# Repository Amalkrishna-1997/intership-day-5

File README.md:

# intership-day-5
internship day 5
PCB layout designing by KICad,

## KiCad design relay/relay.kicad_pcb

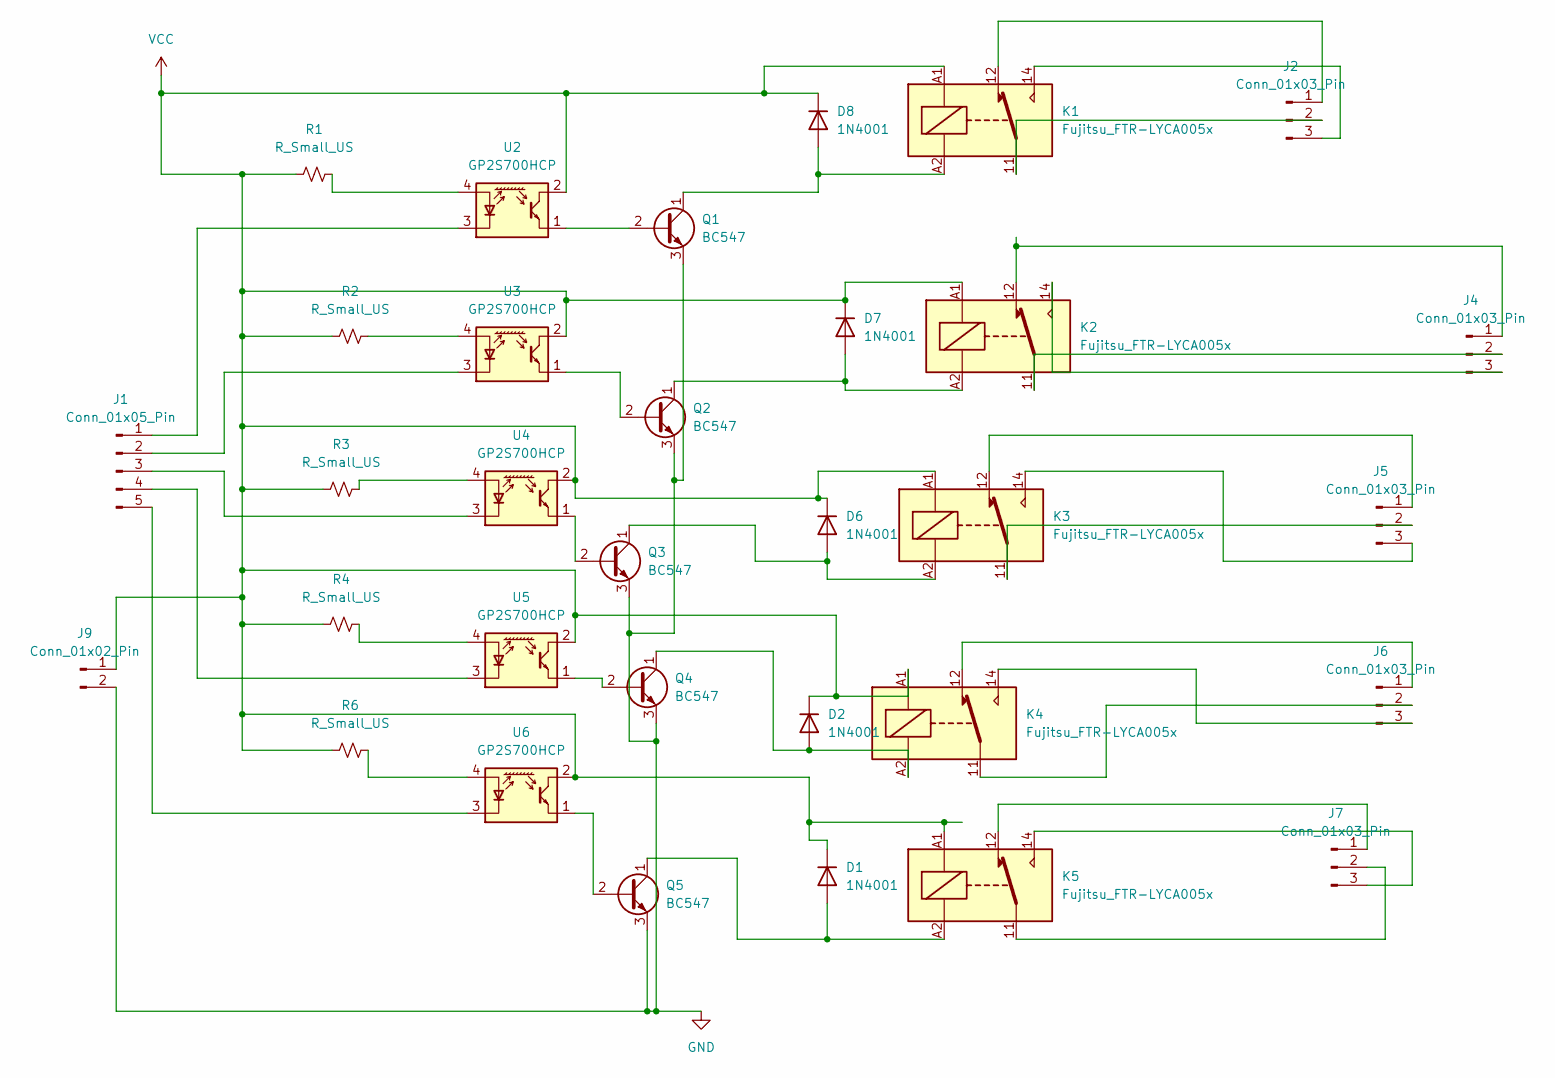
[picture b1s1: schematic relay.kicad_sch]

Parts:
D1, D2, D6, D7, D8: 1N4001; D_DO-41_SOD81_P10.16mm_Horizontal
J1: Conn_01x05_Pin; PinHeader_1x05_P1.00mm_Vertical
J2, J4, J5, J6, J7: Conn_01x03_Pin; PinHeader_1x03_P1.00mm_Vertical
J9: Conn_01x02_Pin; PinHeader_1x02_P1.00mm_Vertical
K1, K2, K3, K4, K5: Fujitsu_FTR-LYCA005x; Relay_SPDT_Schrack-RP-II-1-FormC_RM3.5mm
Q1, Q2, Q3, Q4, Q5: BC547; TO-92_Inline
R1, R2, R3, R4, R6: R_Small_US; R_Axial_DIN0207_L6.3mm_D2.5mm_P10.16mm_Horizontal
U2, U3, U4, U5, U6: GP2S700HCP; Everlight_ITR8307F43

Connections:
GND: J9.2, Q1.3 (E), Q2.3 (E), Q3.3 (E), Q4.3 (E), Q5.3 (E)
unnamed: D1.2 (A), K5.A2, Q5.1 (C)
unnamed: D2.2 (A), K4.A2, Q4.1 (C)
unnamed: D6.2 (A), K3.A2, Q3.1 (C)
unnamed: D7.2 (A), K2.A2, Q2.1 (C)
unnamed: D8.2 (A), K1.A2, Q1.1 (C)
unnamed: J1.1, U2.3 (K)
unnamed: J1.2, U3.3 (K)
unnamed: J1.3, U4.3 (K)
unnamed: J1.4, U5.3 (K)
unnamed: J1.5, U6.3 (K)
unnamed: J2.1, K1.12
unnamed: J2.2, K1.11
unnamed: J2.3, K1.14
unnamed: J4.1, K2.12
unnamed: J4.2, K2.11
unnamed: J4.3, K2.14
unnamed: J5.1, K3.12
unnamed: J5.2, K3.11
unnamed: J5.3, K3.14
unnamed: J6.1, K4.12
unnamed: J6.2, K4.11
unnamed: J6.3, K4.14
unnamed: J7.1, K5.12
unnamed: J7.2, K5.11
unnamed: J7.3, K5.14
unnamed: Q1.2 (B), U2.1
unnamed: Q2.2 (B), U3.1
unnamed: Q3.2 (B), U4.1
unnamed: Q4.2 (B), U5.1
unnamed: Q5.2 (B), U6.1
unnamed: R1.1, U2.4 (A)
unnamed: R2.2, U3.4 (A)
unnamed: R3.2, U4.4 (A)
unnamed: R4.2, U5.4 (A)
unnamed: R6.2, U6.4 (A)
VCC: D1.1 (K), D2.1 (K), D6.1 (K), D7.1 (K), D8.1 (K), J9.1, K1.A1, K2.A1, K3.A1, K4.A1, K5.A1, R1.2, R2.1, R3.1, R4.1, R6.1, U2.2, U3.2, U4.2, U5.2, U6.2

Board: 2 copper layers, 32 parts (0 on the bottom side), 37 nets, no tracks yet.

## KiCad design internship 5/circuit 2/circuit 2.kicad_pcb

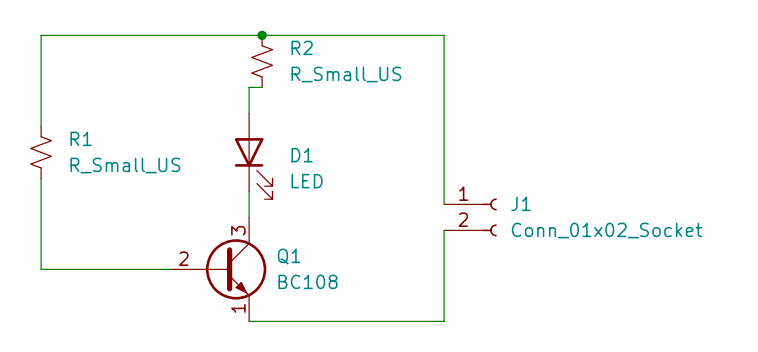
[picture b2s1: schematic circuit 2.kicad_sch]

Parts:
D1: LED; LED_D5.0mm
J1: Conn_01x02_Socket; PinHeader_1x02_P1.00mm_Vertical
Q1: BC108; TO-18-3
R1, R2: R_Small_US; R_Axial_DIN0207_L6.3mm_D2.5mm_P10.16mm_Horizontal

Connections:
unnamed: D1.2 (A), R2.2
unnamed: D1.1 (K), Q1.3 (C)
unnamed: J1.1, R1.1, R2.1
unnamed: J1.2, Q1.1 (E)
unnamed: Q1.2 (B), R1.2

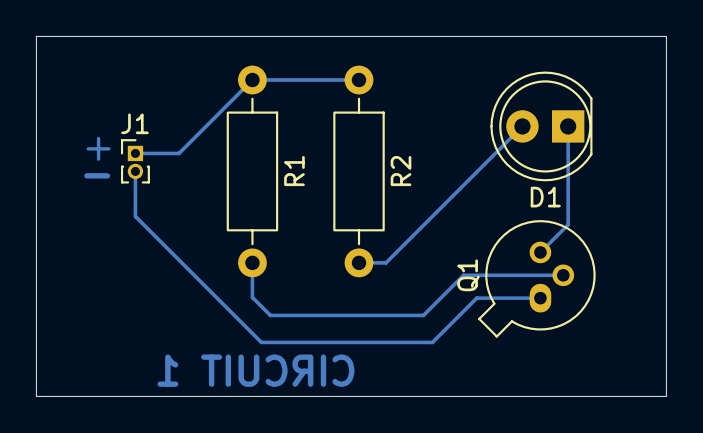
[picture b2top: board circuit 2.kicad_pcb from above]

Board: 2 copper layers, 35.0 x 20.0 mm, 5 parts (0 on the bottom side), 5 nets.

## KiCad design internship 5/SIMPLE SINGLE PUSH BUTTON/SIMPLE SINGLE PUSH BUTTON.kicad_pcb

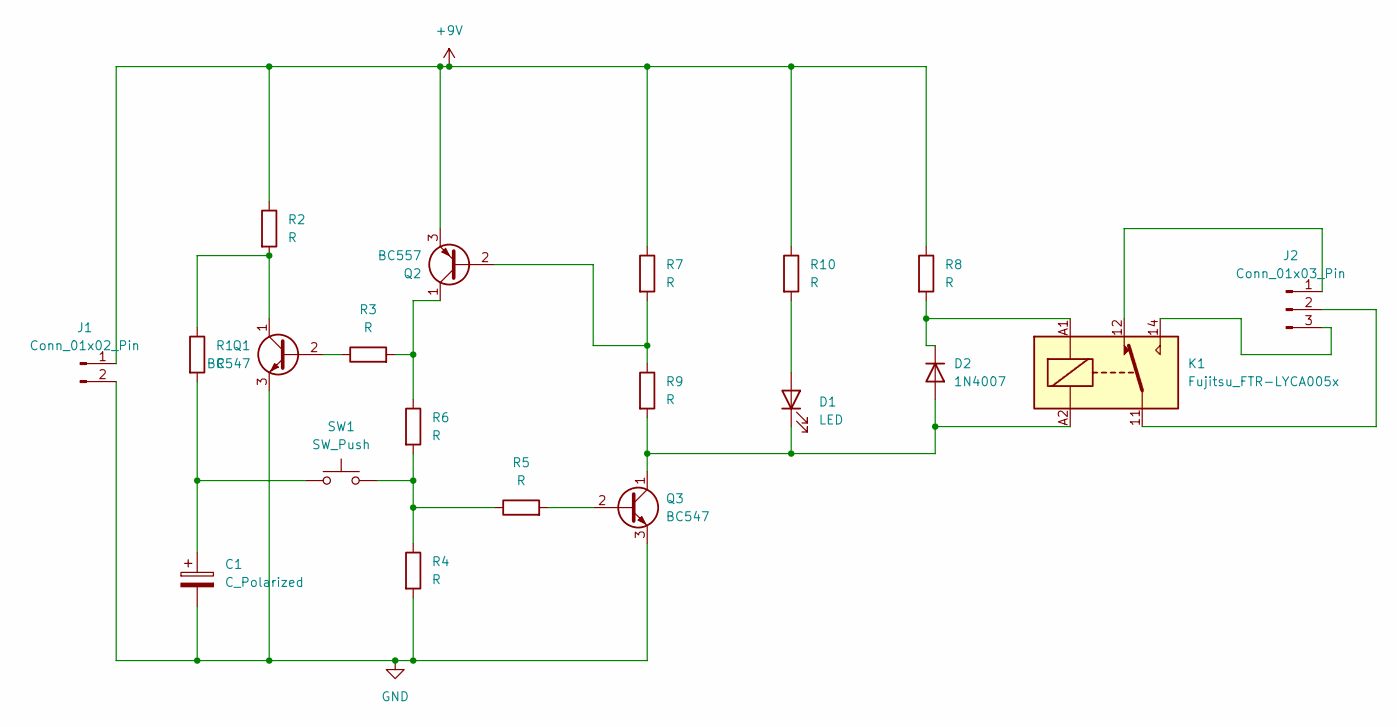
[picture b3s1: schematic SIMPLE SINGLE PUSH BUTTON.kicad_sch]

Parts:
C1: C_Polarized; CP_Radial_D5.0mm_P2.00mm
D1: LED; LED_D5.0mm_Clear
D2: 1N4007; D_DO-41_SOD81_P10.16mm_Horizontal
J1: Conn_01x02_Pin; PinHeader_1x02_P1.00mm_Vertical
J2: Conn_01x03_Pin; PinHeader_1x03_P2.00mm_Vertical
K1: Fujitsu_FTR-LYCA005x; Relay_SPDT_Schrack-RP-II-1-FormC_RM3.5mm
Q1, Q3: BC547; TO-92_Inline
Q2: BC557; TO-92_Inline
R1, R2, R3, R4, R5, R6, R7, R8, R9, R10: R; R_Axial_DIN0207_L6.3mm_D2.5mm_P10.16mm_Horizontal
SW1: SW_Push; SW_PUSH_6mm_H8mm

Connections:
+9V: J1.1, Q2.3 (E), R2.1, R7.1, R8.1, R10.1
GND: C1.2, J1.2, Q1.3 (E), Q3.3 (E), R4.2
unnamed: C1.1, R1.2, SW1.1
unnamed: D1.2 (A), R10.2
unnamed: D1.1 (K), D2.2 (A), K1.A2, Q3.1 (C), R9.2
unnamed: D2.1 (K), K1.A1, R8.2
unnamed: J2.1, K1.12
unnamed: J2.2, K1.11
unnamed: J2.3, K1.14
unnamed: Q1.2 (B), R3.1
unnamed: Q1.1 (C), R1.1, R2.2
unnamed: Q2.2 (B), R7.2, R9.1
unnamed: Q2.1 (C), R3.2, R6.1
unnamed: Q3.2 (B), R5.2
unnamed: R4.1, R5.1, R6.2, SW1.2

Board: 2 copper layers, 20 parts (0 on the bottom side), 15 nets, no tracks yet.
